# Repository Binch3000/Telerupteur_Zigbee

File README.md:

# Telerupteur ZigBee FR
Carte de commande pour le contrôle d'un télérupteur avec retour d'état de l'éclairage.

## Pourquoi
Le télérupteur Legrand Drivia 1.991.21 ne remplis pas mon cahier des charges.
J'ai un bon vieux télérupteur à bobine, avec lequel il est possible d'avoir des témoins visuels sur chaque bouton-poussoir. (LED)
L'autre avantage, c'est qu'il se monte comme un bouton-poussoir à l'emplacement voulu.
Il faut également récupérer une alimentation (la même que le télérupteur) ainsi que la puissance de l'éclairage.  

## Liste des composants

Détail dans le ficier ibom.html
- [µP ESP32H2 SuperMini (x1)](https://fr.aliexpress.com/item/1005007235112528.html)
- [Relais HF49FD (x1) HF49FD-005-1H11](https://fr.aliexpress.com/item/1005005163929430.html)

Pour le moment le circuit est maintenu chez moi avec cette boite, dans une GTL. Prendre la version 50-100mm suffit. https://fr.aliexpress.com/item/32624897936.html

## Schéma
- Câblage
- Installation perso

## Évolution :
En fonction des demandes, il sera possible de continuer à développer le projet.
Ceci n'est que quelques idées que j'avais en tête.

- Création d'une boite à imprimer en 3D
- Mise à jour par OTA

## Divers
J'ai la possibilité d'expédier une carte vierge ou même prêt à l'utilisation selon vos besoins.

# ZigBee Remote Switch EN
Control board for controlling a remote switch with lighting status feedback.

## Why
The Legrand Drivia 1.991.21 remote switch doesn't meet my requirements.
I have a good old-fashioned coil-type remote switch, which allows for visual indicators on each push button (LEDs).
Another advantage is that it can be mounted like a push button in the desired location.
It also requires a power supply (the same as the remote switch) and the power supply for the lighting.

## Component List

Details in the ibom.html file
- [µP ESP32H2 SuperMini (x1)](https://fr.aliexpress.com/item/1005007235112528.html)
- [HF49FD Relay (x1) HF49FD-005-1H11](https://fr.aliexpress.com/item/1005005163929430.html)

For now, the circuit is maintained at home with this box, in a GTL. The 50-100mm version is sufficient. https://fr.aliexpress.com/item/32624897936.html

## Diagram
- Wiring
- Custom Installation

## Evolution:
Depending on demand, it will be possible to continue developing the project.
These are just a few ideas I had in mind.

- Creation of a 3D printed box
- OTA updates

## Miscellaneous
I can ship a blank card or even a ready-to-use one, depending on your needs.

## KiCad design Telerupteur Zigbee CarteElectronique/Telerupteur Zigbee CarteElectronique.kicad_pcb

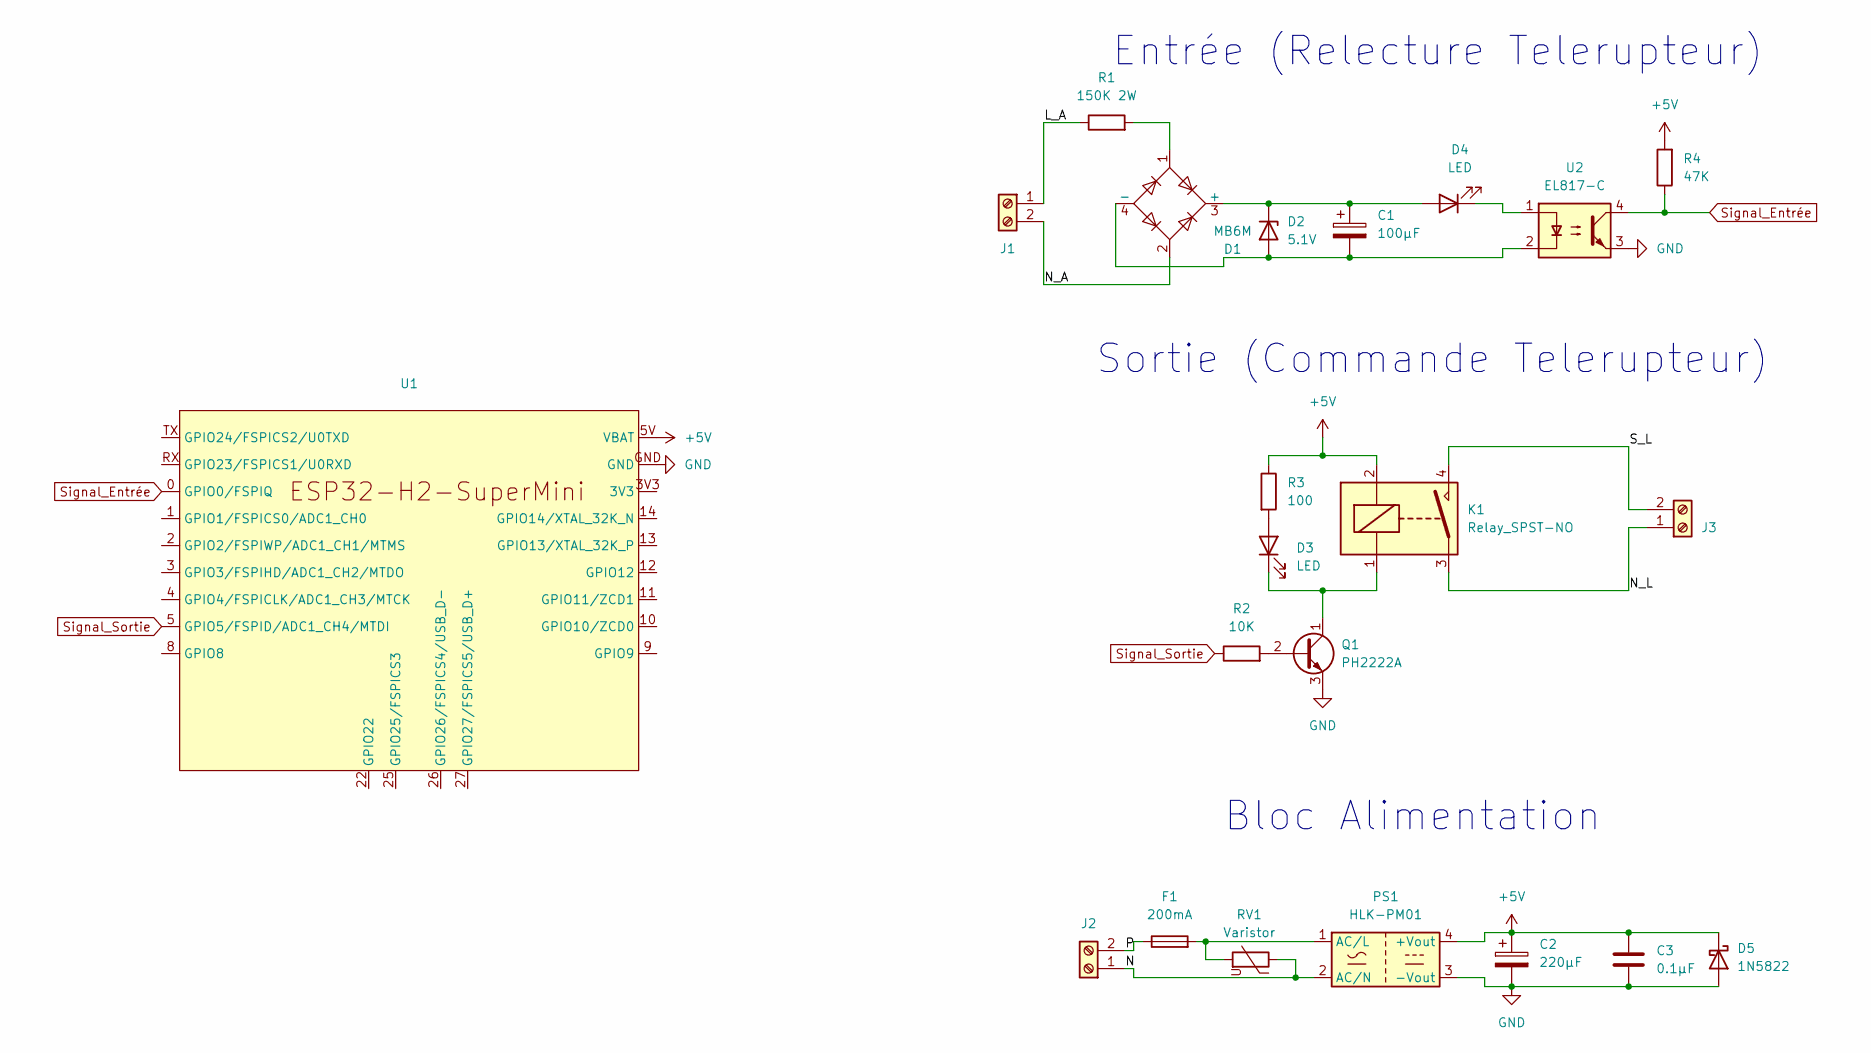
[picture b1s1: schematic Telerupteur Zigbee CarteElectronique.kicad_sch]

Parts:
C1: 100µF; CP_Radial_D6.3mm_P2.50mm
C2: 220µF; CP_Radial_D6.3mm_P2.50mm
C3: 0.1µF; C_Rect_L10.3mm_W5.0mm_P7.50mm_MKS4
D1: MB6M; Diode_Bridge_DIP-4_W5.08mm_P2.54mm
D2: 5.1V; D_A-405_P7.62mm_Horizontal
D3, D4: LED; LED_D3.0mm
D5: 1N5822; D_T-1_P10.16mm_Horizontal
F1: 200mA; Fuseholder_Cylinder-5x20mm_Schurter_FAB_0031-355x_Horizonta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
J1, J2, J3: Screw_Terminal_01x02; TerminalBlock_Phoenix_PT-1,5-2-5.0-H_1x02_P5.00mm_Horizontal
K1: Relay_SPST-NO; HF49FD
PS1: HLK-PM01; Converter_ACDC_Hi-Link_HLK-PMxx
Q1: PH2222A; TO-92L_Inline_Wide
R1: 150K 2W; R_Axial_DIN0516_L15.5mm_D5.0mm_P20.32mm_Horizontal
R2: 10K; R_Axial_DIN0207_L6.3mm_D2.5mm_P10.16mm_Horizontal
R3: 100; R_Axial_DIN0207_L6.3mm_D2.5mm_P10.16mm_Horizontal
R4: 47K; R_Axial_DIN0207_L6.3mm_D2.5mm_P10.16mm_Horizontal
RV1: Varistor; RV_Disc_D12mm_W3.9mm_P7.5mm
U1: ESP32-H2-SuperMini
U2: EL817-C; DIP-4_W7.62mm

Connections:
+5V: C2.1, C3.1, D5.1 (K), K1.2, PS1.4 (+Vout), R3.1, R4.2, U1.5V (VBAT)
/L_A: J1.1, R1.1
/N: J2.1, PS1.2 (AC/N), RV1.1
/N_A: D1.2, J1.2
/N_L: J3.1, K1.3
/P: F1.1, J2.2
/S_L: J3.2, K1.4
GND: C2.2, C3.2, D5.2 (A), PS1.3 (-Vout), Q1.3 (E), U1.GND, U2.3
unnamed: C1.1, D1.3 (+), D2.1 (K), D4.2 (A)
unnamed: C1.2, D1.4 (-), D2.2 (A), U2.2
unnamed: D1.1, R1.2
unnamed: D3.2 (A), R3.2
unnamed: D3.1 (K), K1.1, Q1.1 (C)
unnamed: D4.1 (K), U2.1
unnamed: F1.2, PS1.1 (AC/L), RV1.2
unnamed: Q1.2 (B), R2.2
Signal_Entrée: R4.1, U1.0 (GPIO0/FSPIQ), U2.4
Signal_Sortie: R2.1, U1.5 (GPIO5/FSPID/ADC1_CH4/MTDI)

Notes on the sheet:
Bloc Alimentation
Entrée (Relecture Telerupteur)
Sortie (Commande Telerupteur)

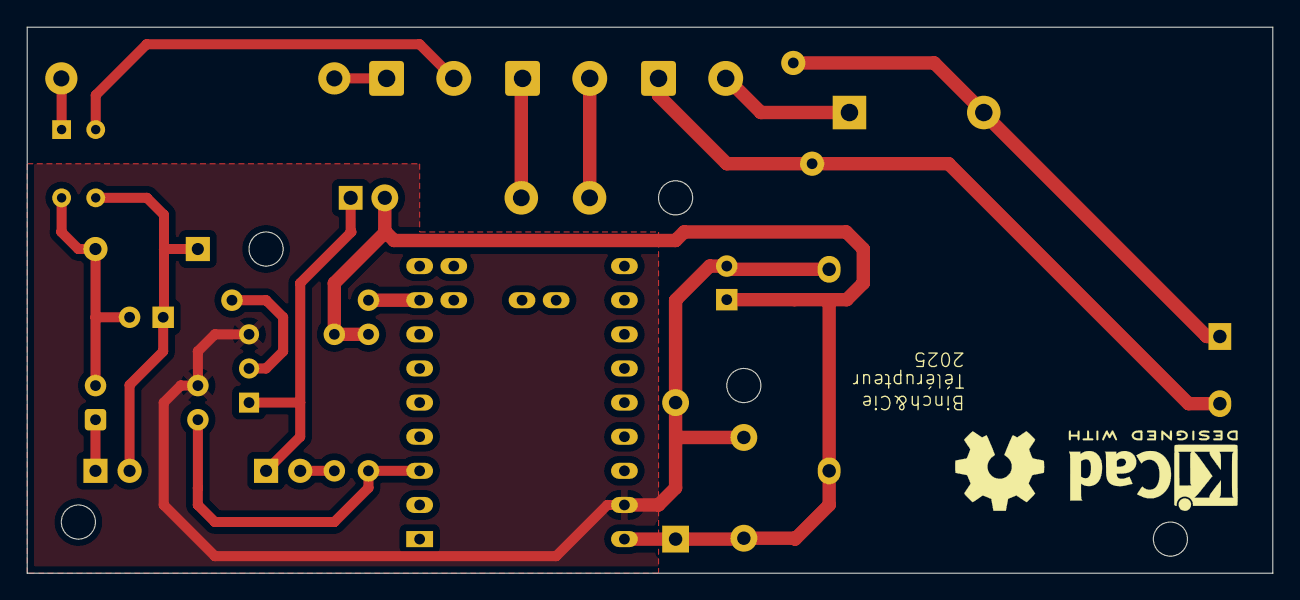
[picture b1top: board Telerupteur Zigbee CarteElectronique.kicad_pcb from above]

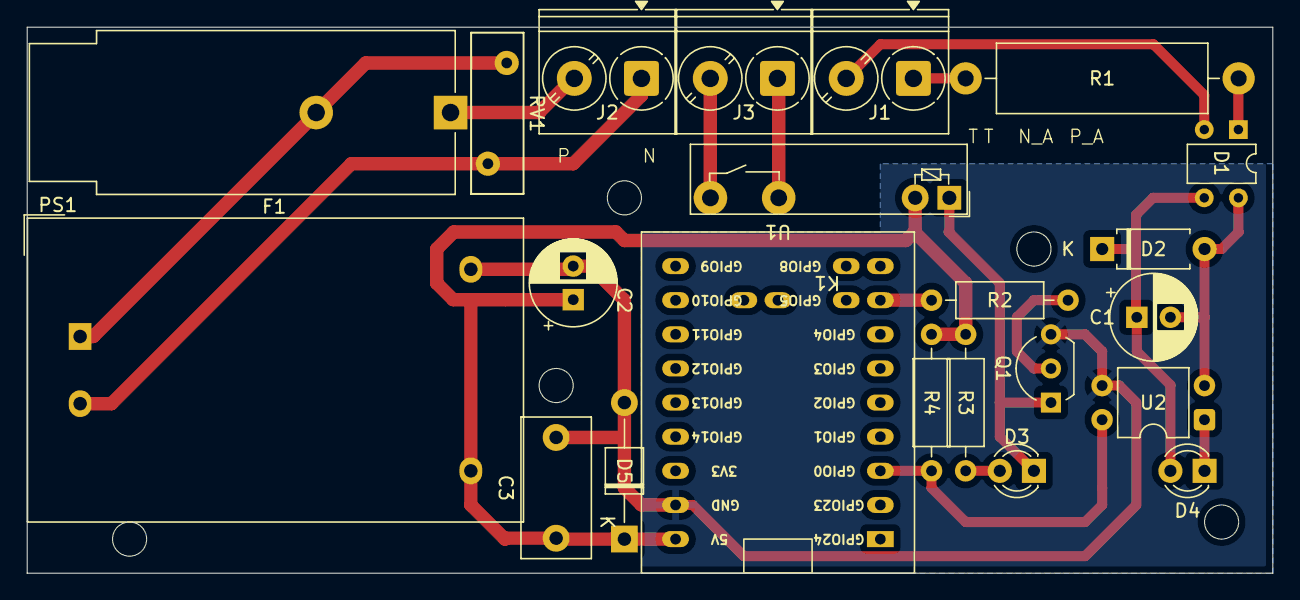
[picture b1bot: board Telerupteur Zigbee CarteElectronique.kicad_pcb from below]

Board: 2 copper layers, 92.7 x 40.6 mm, 22 parts (22 on the bottom side), 18 nets.

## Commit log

2025-09-23 Rename Capture d’écran 2025-09-23 212836.png to ZHA_Telerupteur_Zigbee.png
2026-05-14 Evolution majeure
    Simplification d'utilisation et d'installation.
    Plus besoin d'intervenir dans Home Assistant
2026-05-14 Update README.md
    Maj V2
